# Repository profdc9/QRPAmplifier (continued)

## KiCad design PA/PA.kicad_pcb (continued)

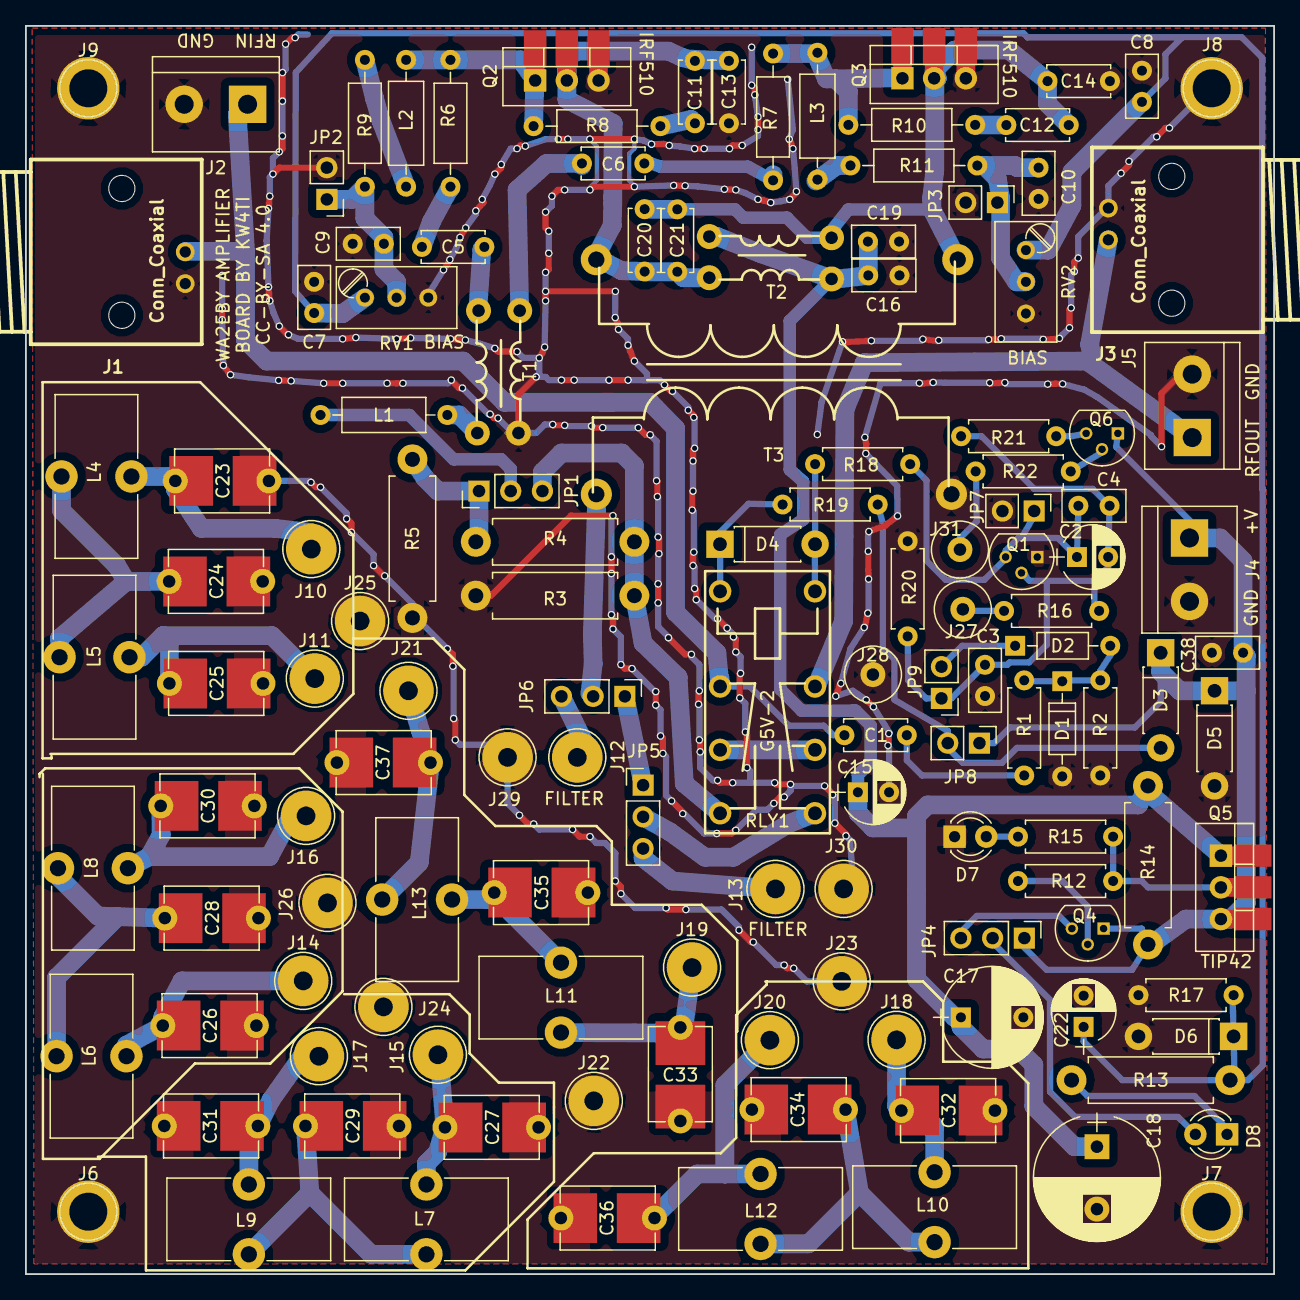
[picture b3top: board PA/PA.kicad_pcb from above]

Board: 2 copper layers, 100.0 x 100.0 mm, 133 parts (0 on the bottom side), 63 nets.

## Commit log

2019-02-13 Made filter capacitors mica or 1206 SMT
2019-02-13 Add transmit disable switch
2019-02-14 Artwork fix
2019-02-14 Tightened up components
2019-02-14 Last commit has wrong PCB screenshot
2019-02-14 Delete PA-board.png
    Problem with committing this !
2019-02-14 Graphic not pushed. why?
2019-02-15 Some more comitization
2019-02-16 Moved T!
2019-02-20 Changed overcurrent circuit...
2019-02-21 Added via fences
2019-06-01 Added more convenient pads for TO220 devices
2019-06-08 JLCPCB order tested
2019-06-20 Added documentation
2019-06-28 Added BiggerPA
2019-06-28 Added series inductor to gates
2019-06-30 Added Filter
2019-07-03 Changed to 7805 regulator
2019-07-12 Added some extra protection and fixed labels on Filter
2019-07-20 Added gate resistors to BiggerPA
2019-10-01 Changed rig RX/TX control
2019-10-20 Fixed polarity of rig RXTX relay grounding
2019-10-22 Oops swapped pictures
2019-11-13 Added tandem match to sense power to filter board
2020-04-29 Moved series resistor closer to common drain amplifier to prevent oscillation
